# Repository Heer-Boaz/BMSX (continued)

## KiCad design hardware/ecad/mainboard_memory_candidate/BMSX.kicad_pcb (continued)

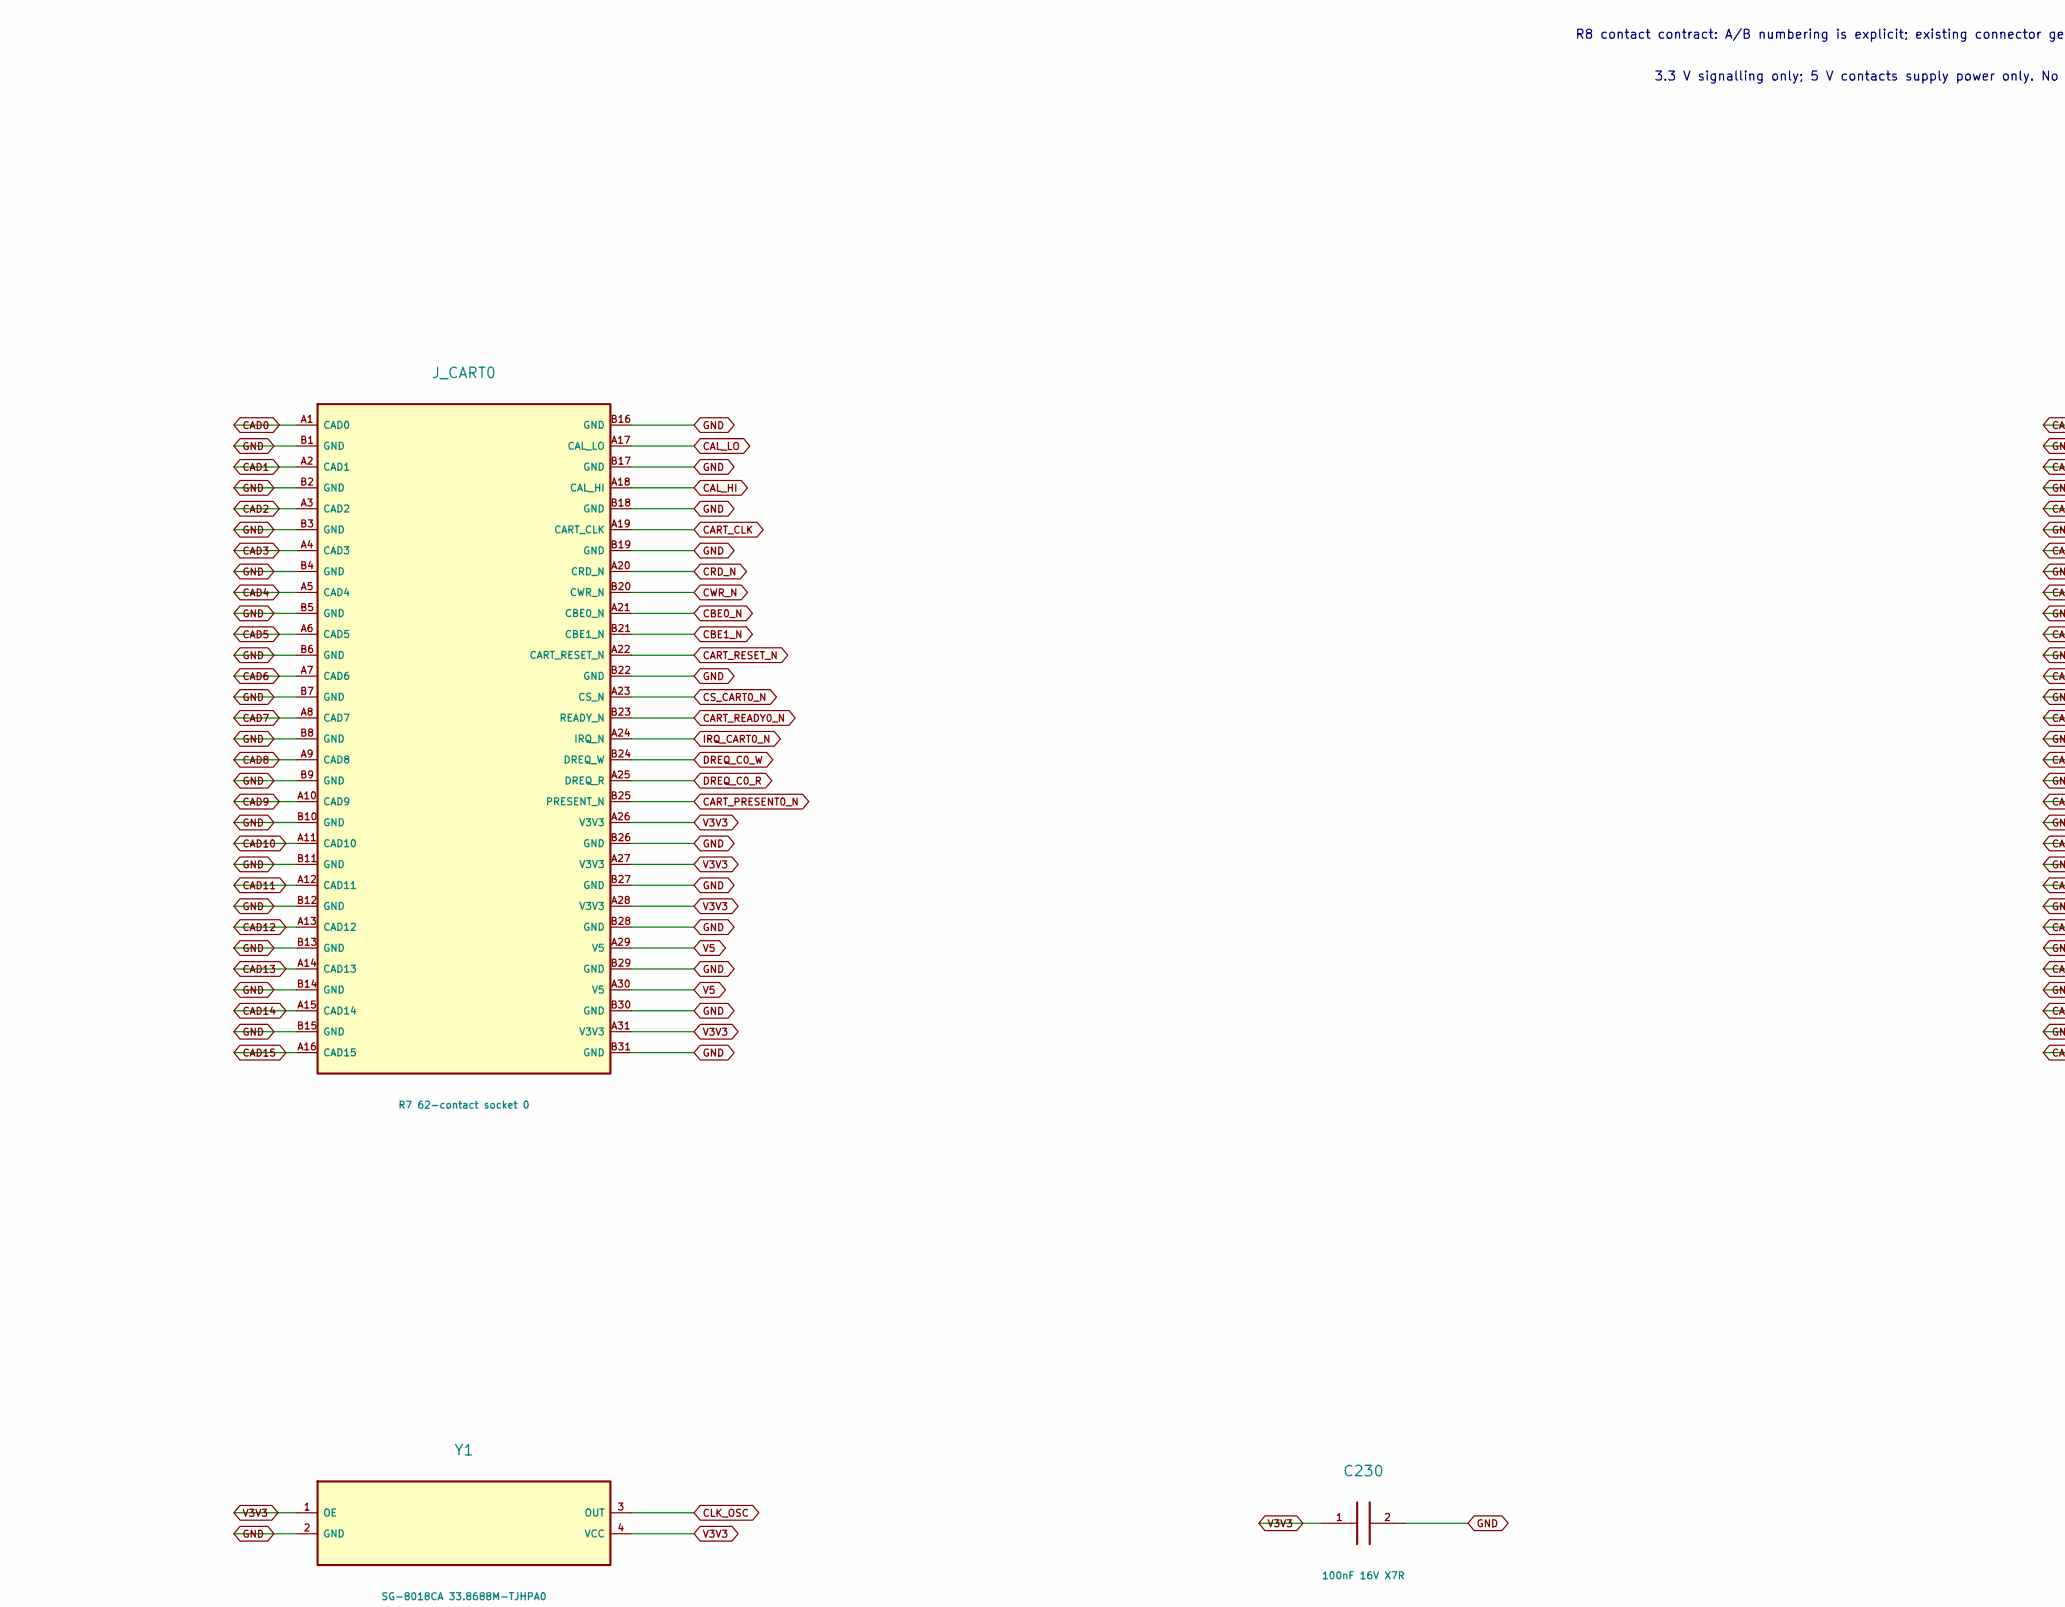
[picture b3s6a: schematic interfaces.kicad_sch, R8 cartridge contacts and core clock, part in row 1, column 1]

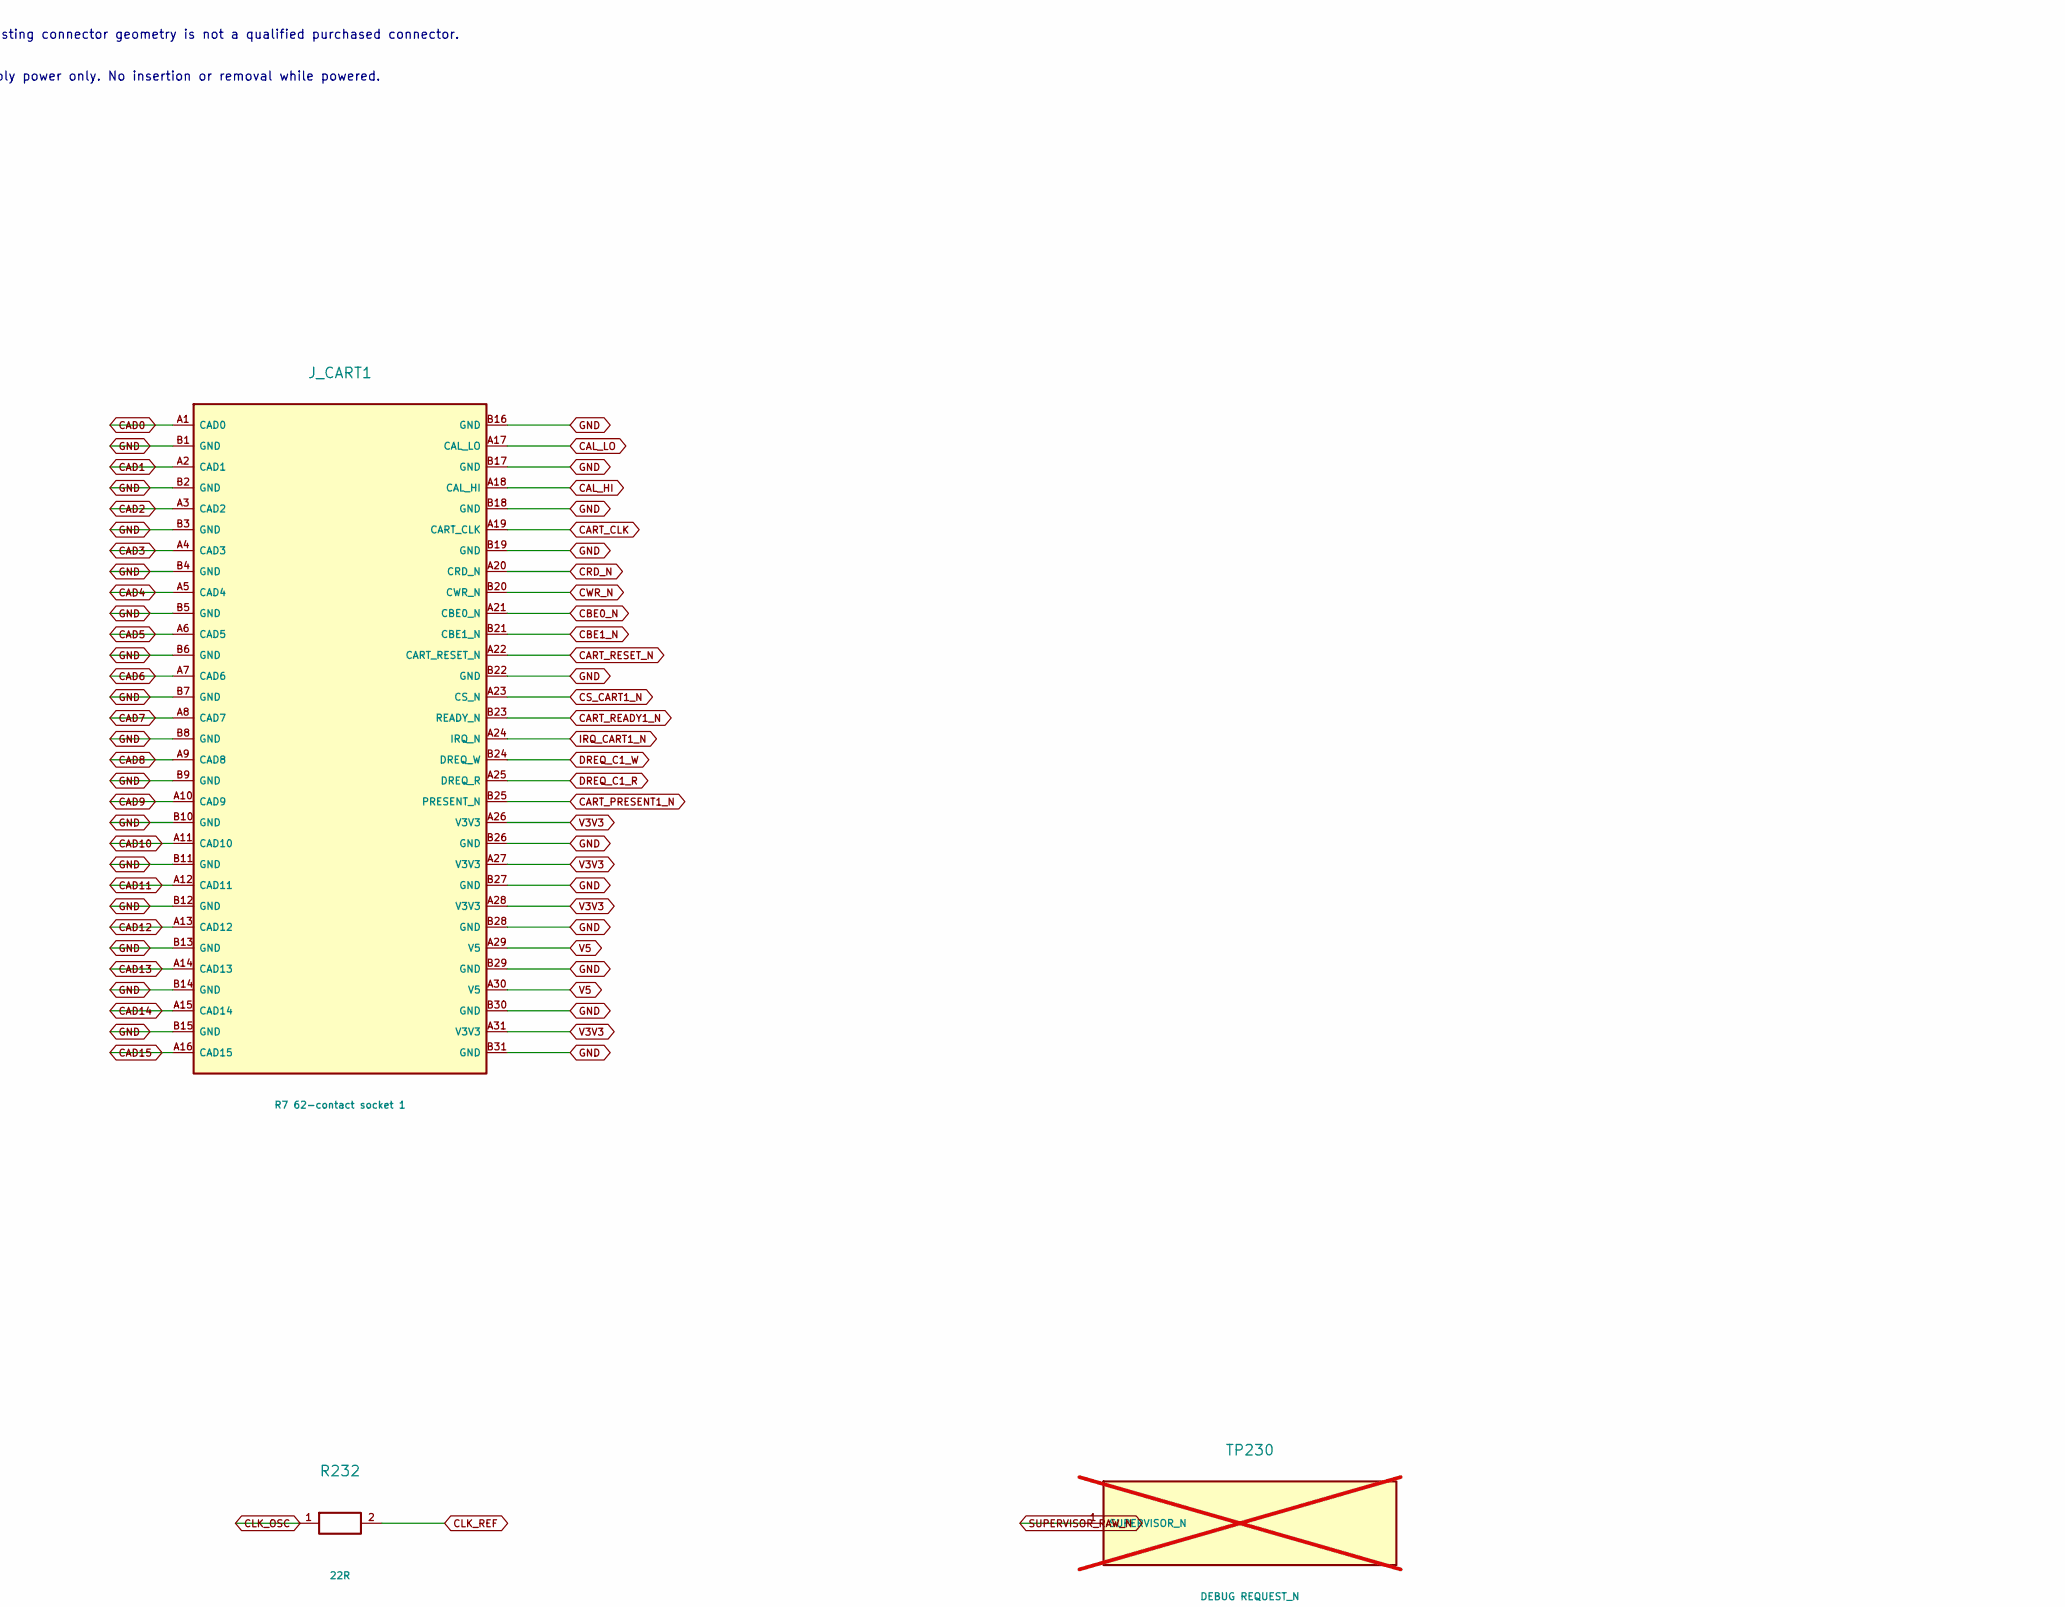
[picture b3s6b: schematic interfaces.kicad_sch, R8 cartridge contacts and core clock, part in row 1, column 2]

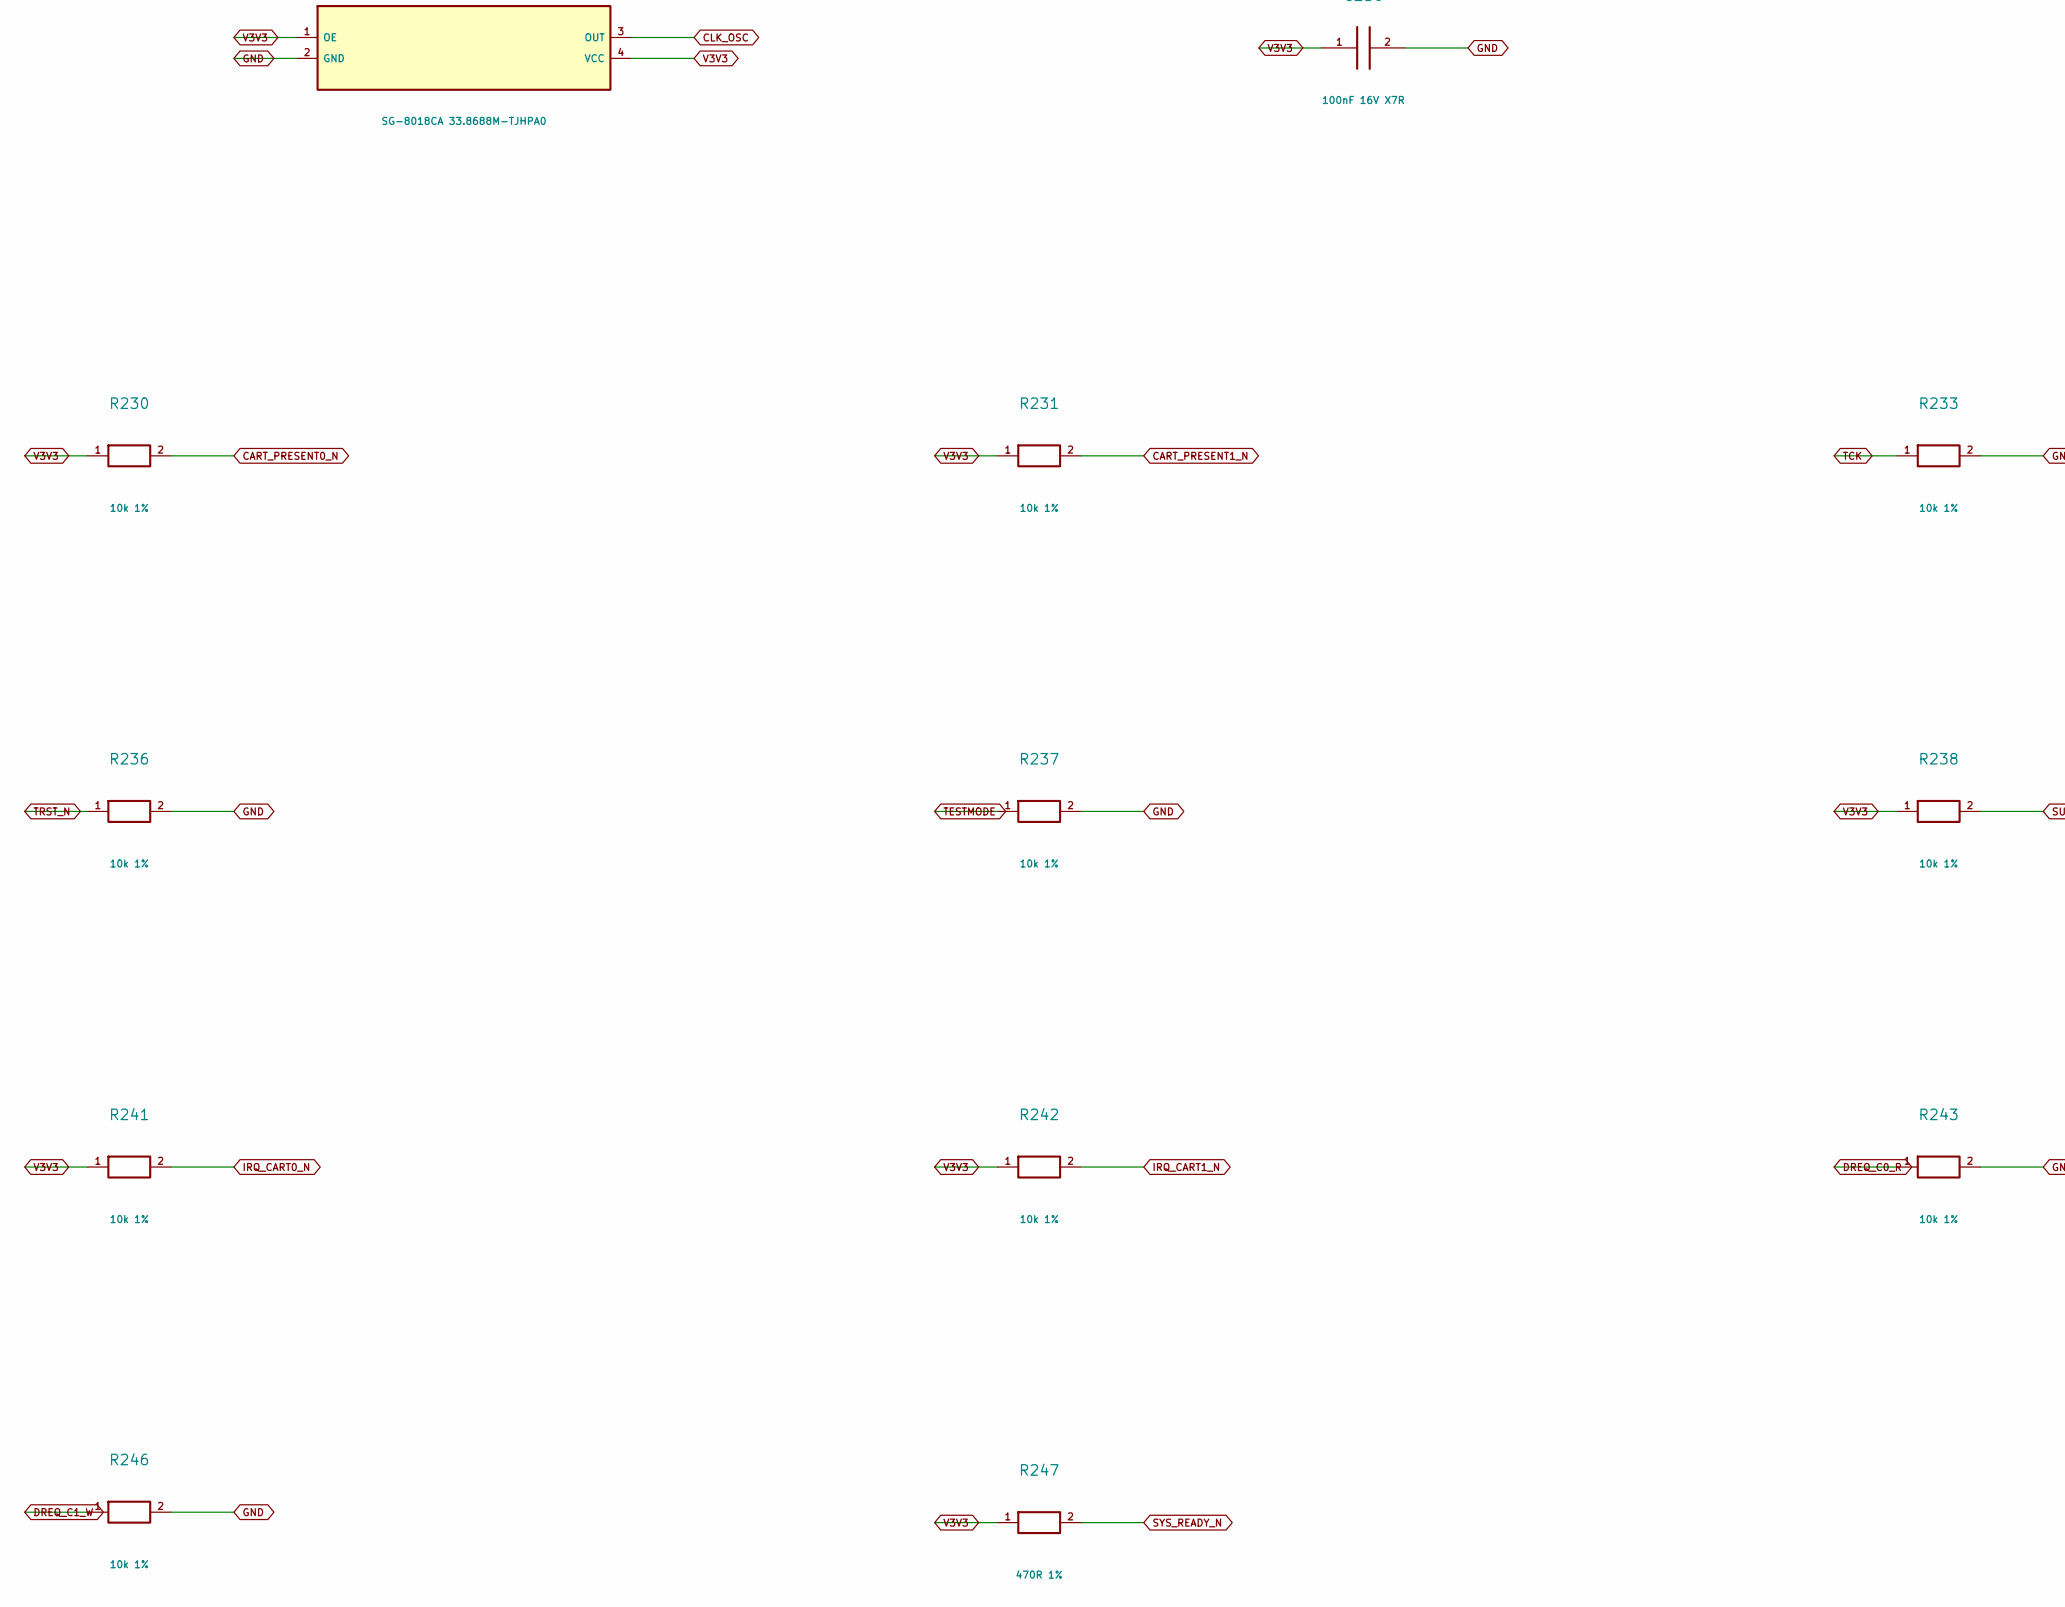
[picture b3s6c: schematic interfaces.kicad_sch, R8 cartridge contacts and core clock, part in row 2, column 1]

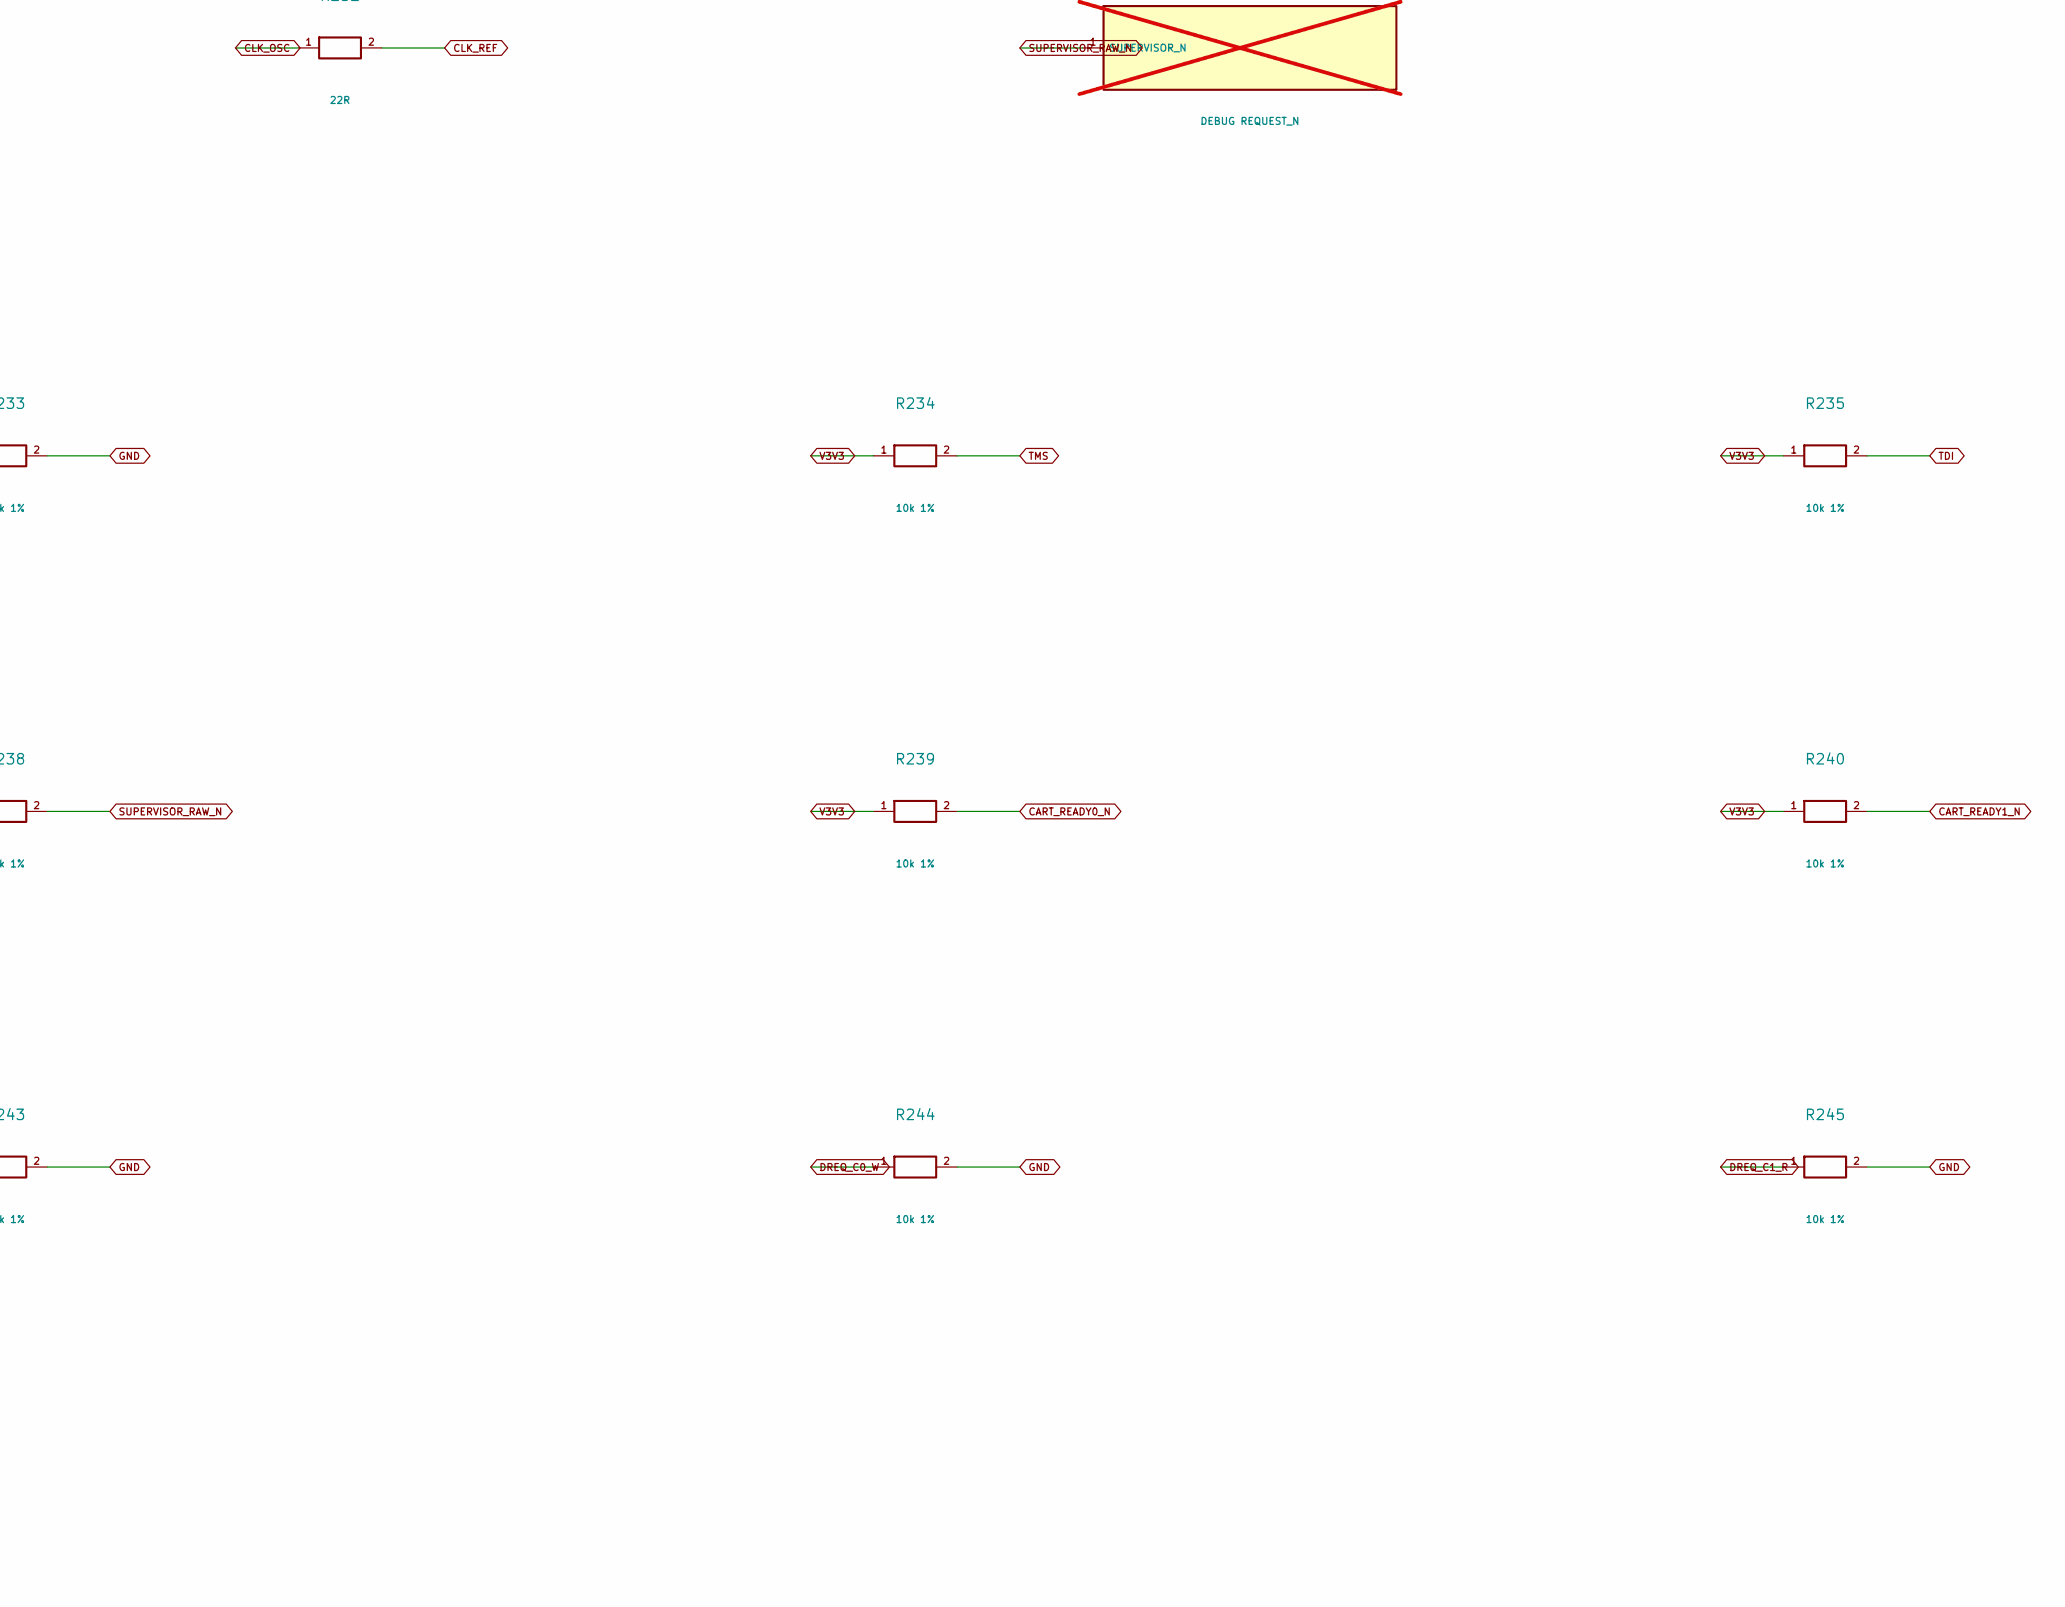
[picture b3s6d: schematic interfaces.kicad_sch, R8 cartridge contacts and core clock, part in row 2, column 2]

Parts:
C230: 100nF 16V X7R; C230
J_CART0: R7 62-contact socket 0; J_CART0; MPN 395-062-520-202
J_CART1: R7 62-contact socket 1; J_CART1; MPN 395-062-520-202
R230: 10k 1%; R230
R231: 10k 1%; R231
R232: 22R; R232
R233: 10k 1%; R233
R234: 10k 1%; R234
R235: 10k 1%; R235
R236: 10k 1%; R236
R237: 10k 1%; R237
R238: 10k 1%; R238
R239: 10k 1%; R239
R240: 10k 1%; R240
R241: 10k 1%; R241
R242: 10k 1%; R242
R243: 10k 1%; R243
R244: 10k 1%; R244
R245: 10k 1%; R245
R246: 10k 1%; R246
R247: 470R 1%; R247
TP230: DEBUG REQUEST_N; TP230; not fitted
Y1: SG-8018CA 33.8688M-TJHPA0; Y1

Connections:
CAD0: J_CART0.A1 (CAD0), J_CART1.A1 (CAD0); also elsewhere on the board
CAD1: J_CART0.A2 (CAD1), J_CART1.A2 (CAD1); also elsewhere on the board
CAD2: J_CART0.A3 (CAD2), J_CART1.A3 (CAD2); also elsewhere on the board
CAD3: J_CART0.A4 (CAD3), J_CART1.A4 (CAD3); also elsewhere on the board
CAD4: J_CART0.A5 (CAD4), J_CART1.A5 (CAD4); also elsewhere on the board
CAD5: J_CART0.A6 (CAD5), J_CART1.A6 (CAD5); also elsewhere on the board
CAD6: J_CART0.A7 (CAD6), J_CART1.A7 (CAD6); also elsewhere on the board
CAD7: J_CART0.A8 (CAD7), J_CART1.A8 (CAD7); also elsewhere on the board
CAD8: J_CART0.A9 (CAD8), J_CART1.A9 (CAD8); also elsewhere on the board
CAD9: J_CART0.A10 (CAD9), J_CART1.A10 (CAD9); also elsewhere on the board
CAD10: J_CART0.A11 (CAD10), J_CART1.A11 (CAD10); also elsewhere on the board
CAD11: J_CART0.A12 (CAD11), J_CART1.A12 (CAD11); also elsewhere on the board
CAD12: J_CART0.A13 (CAD12), J_CART1.A13 (CAD12); also elsewhere on the board
CAD13: J_CART0.A14 (CAD13), J_CART1.A14 (CAD13); also elsewhere on the board
CAD14: J_CART0.A15 (CAD14), J_CART1.A15 (CAD14); also elsewhere on the board
CAD15: J_CART0.A16 (CAD15), J_CART1.A16 (CAD15); also elsewhere on the board
CAL_HI: J_CART0.A18 (CAL_HI), J_CART1.A18 (CAL_HI); also elsewhere on the board
CAL_LO: J_CART0.A17 (CAL_LO), J_CART1.A17 (CAL_LO); also elsewhere on the board
CART_CLK: J_CART0.A19 (CART_CLK), J_CART1.A19 (CART_CLK); also elsewhere on the board
CART_PRESENT0_N: J_CART0.B25 (PRESENT_N), R230.2; also elsewhere on the board
CART_PRESENT1_N: J_CART1.B25 (PRESENT_N), R231.2; also elsewhere on the board
CART_READY0_N: J_CART0.B23 (READY_N), R239.2; also elsewhere on the board
CART_READY1_N: J_CART1.B23 (READY_N), R240.2; also elsewhere on the board
CART_RESET_N: J_CART0.A22 (CART_RESET_N), J_CART1.A22 (CART_RESET_N); also elsewhere on the board
CBE0_N: J_CART0.A21 (CBE0_N), J_CART1.A21 (CBE0_N); also elsewhere on the board
CBE1_N: J_CART0.B21 (CBE1_N), J_CART1.B21 (CBE1_N); also elsewhere on the board
CLK_OSC: R232.1, Y1.3 (OUT)
CLK_REF: R232.2; also elsewhere on the board
CRD_N: J_CART0.A20 (CRD_N), J_CART1.A20 (CRD_N); also elsewhere on the board
CS_CART0_N: J_CART0.A23 (CS_N); also elsewhere on the board
CS_CART1_N: J_CART1.A23 (CS_N); also elsewhere on the board
CWR_N: J_CART0.B20 (CWR_N), J_CART1.B20 (CWR_N); also elsewhere on the board
DREQ_C0_R: J_CART0.A25 (DREQ_R), R243.1; also elsewhere on the board
DREQ_C0_W: J_CART0.B24 (DREQ_W), R244.1; also elsewhere on the board
DREQ_C1_R: J_CART1.A25 (DREQ_R), R245.1; also elsewhere on the board
DREQ_C1_W: J_CART1.B24 (DREQ_W), R246.1; also elsewhere on the board
GND: C230.2, J_CART0.B1 (GND), J_CART0.B2 (GND), J_CART0.B3 (GND), J_CART0.B4 (GND), J_CART0.B5 (GND), J_CART0.B6 (GND), J_CART0.B7 (GND), J_CART0.B8 (GND), J_CART0.B9 (GND), J_CART0.B10 (GND), J_CART0.B11 (GND), J_CART0.B12 (GND), J_CART0.B13 (GND), J_CART0.B14 (GND), J_CART0.B15 (GND), J_CART0.B16 (GND), J_CART0.B17 (GND), J_CART0.B18 (GND), J_CART0.B19 (GND), J_CART0.B22 (GND), J_CART0.B26 (GND), J_CART0.B27 (GND), J_CART0.B28 (GND), J_CART0.B29 (GND), J_CART0.B30 (GND), J_CART0.B31 (GND), J_CART1.B1 (GND), J_CART1.B2 (GND), J_CART1.B3 (GND), J_CART1.B4 (GND), J_CART1.B5 (GND), J_CART1.B6 (GND), J_CART1.B7 (GND), J_CART1.B8 (GND), J_CART1.B9 (GND), J_CART1.B10 (GND), J_CART1.B11 (GND), J_CART1.B12 (GND), J_CART1.B13 (GND), J_CART1.B14 (GND), J_CART1.B15 (GND), J_CART1.B16 (GND), J_CART1.B17 (GND), J_CART1.B18 (GND), J_CART1.B19 (GND), J_CART1.B22 (GND), J_CART1.B26 (GND), J_CART1.B27 (GND), J_CART1.B28 (GND), J_CART1.B29 (GND), J_CART1.B30 (GND), J_CART1.B31 (GND), R233.2, R236.2, R237.2, R243.2, R244.2, R245.2, R246.2, Y1.2 (GND); also elsewhere on the board
IRQ_CART0_N: J_CART0.A24 (IRQ_N), R241.2; also elsewhere on the board
IRQ_CART1_N: J_CART1.A24 (IRQ_N), R242.2; also elsewhere on the board
SUPERVISOR_RAW_N: R238.2, TP230.1 (SUPERVISOR_N); also elsewhere on the board
SYS_READY_N: R247.2; also elsewhere on the board
TCK: R233.1; also elsewhere on the board
TDI: R235.2; also elsewhere on the board
TESTMODE: R237.1; also elsewhere on the board
TMS: R234.2; also elsewhere on the board
TRST_N: R236.1; also elsewhere on the board
V3V3: C230.1, J_CART0.A26 (V3V3), J_CART0.A27 (V3V3), J_CART0.A28 (V3V3), J_CART0.A31 (V3V3), J_CART1.A26 (V3V3), J_CART1.A27 (V3V3), J_CART1.A28 (V3V3), J_CART1.A31 (V3V3), R230.1, R231.1, R234.1, R235.1, R238.1, R239.1, R240.1, R241.1, R242.1, R247.1, Y1.1 (OE), Y1.4 (VCC); also elsewhere on the board
V5: J_CART0.A29 (V5), J_CART0.A30 (V5), J_CART1.A29 (V5), J_CART1.A30 (V5); also elsewhere on the board

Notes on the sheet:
R8 contact contract: A/B numbering is explicit; existing connector geometry is not a qualified purchased connector.
3.3 V signalling only; 5 V contacts supply power only. No insertion or removal while powered.
